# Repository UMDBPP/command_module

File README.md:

# ```</CMD>```

Command is the primary tracking payload flown by BPP. This repository contains design files and software required to run the current version of command.

Current POC:
Shipman

 ## Design Priciples
As the command module needs to fly on every flight mass reduction is a primary focus. For this reason a switch from perfboard to custom PCB's was done, and a substantial reduction in box volume is underway. Reliability is incredibly important and for this reason the payload operates its tracking systems in a full 4N redundant method.
### Tracking systems include (system/function):
#### 2x LiteAPRS 2m transmitters on 144.390 MHz
In flight position updates every minute. By nature of APRS tracking in hilly terrain unlikely to receive exact coordinates under 500m unless operating our own radios.
#### 1x SPOT Trace Tracker
COTS tracker from SPOT. Gives exact coordinates on landing.
#### 1x BITS (Balloon Iridium Telemetry System)
Exact coordinates throughout the flight, variable transmission rate 1min-15minutes (technically 10s-inf). Datalogger. XBee 900 HP allows for commands to be relayed through Iridium to other payloads and telemetry from payloads to be sent to ground. Possibility of ground to payload XBee communication without Iridium allowing for low latency high rate commanding.

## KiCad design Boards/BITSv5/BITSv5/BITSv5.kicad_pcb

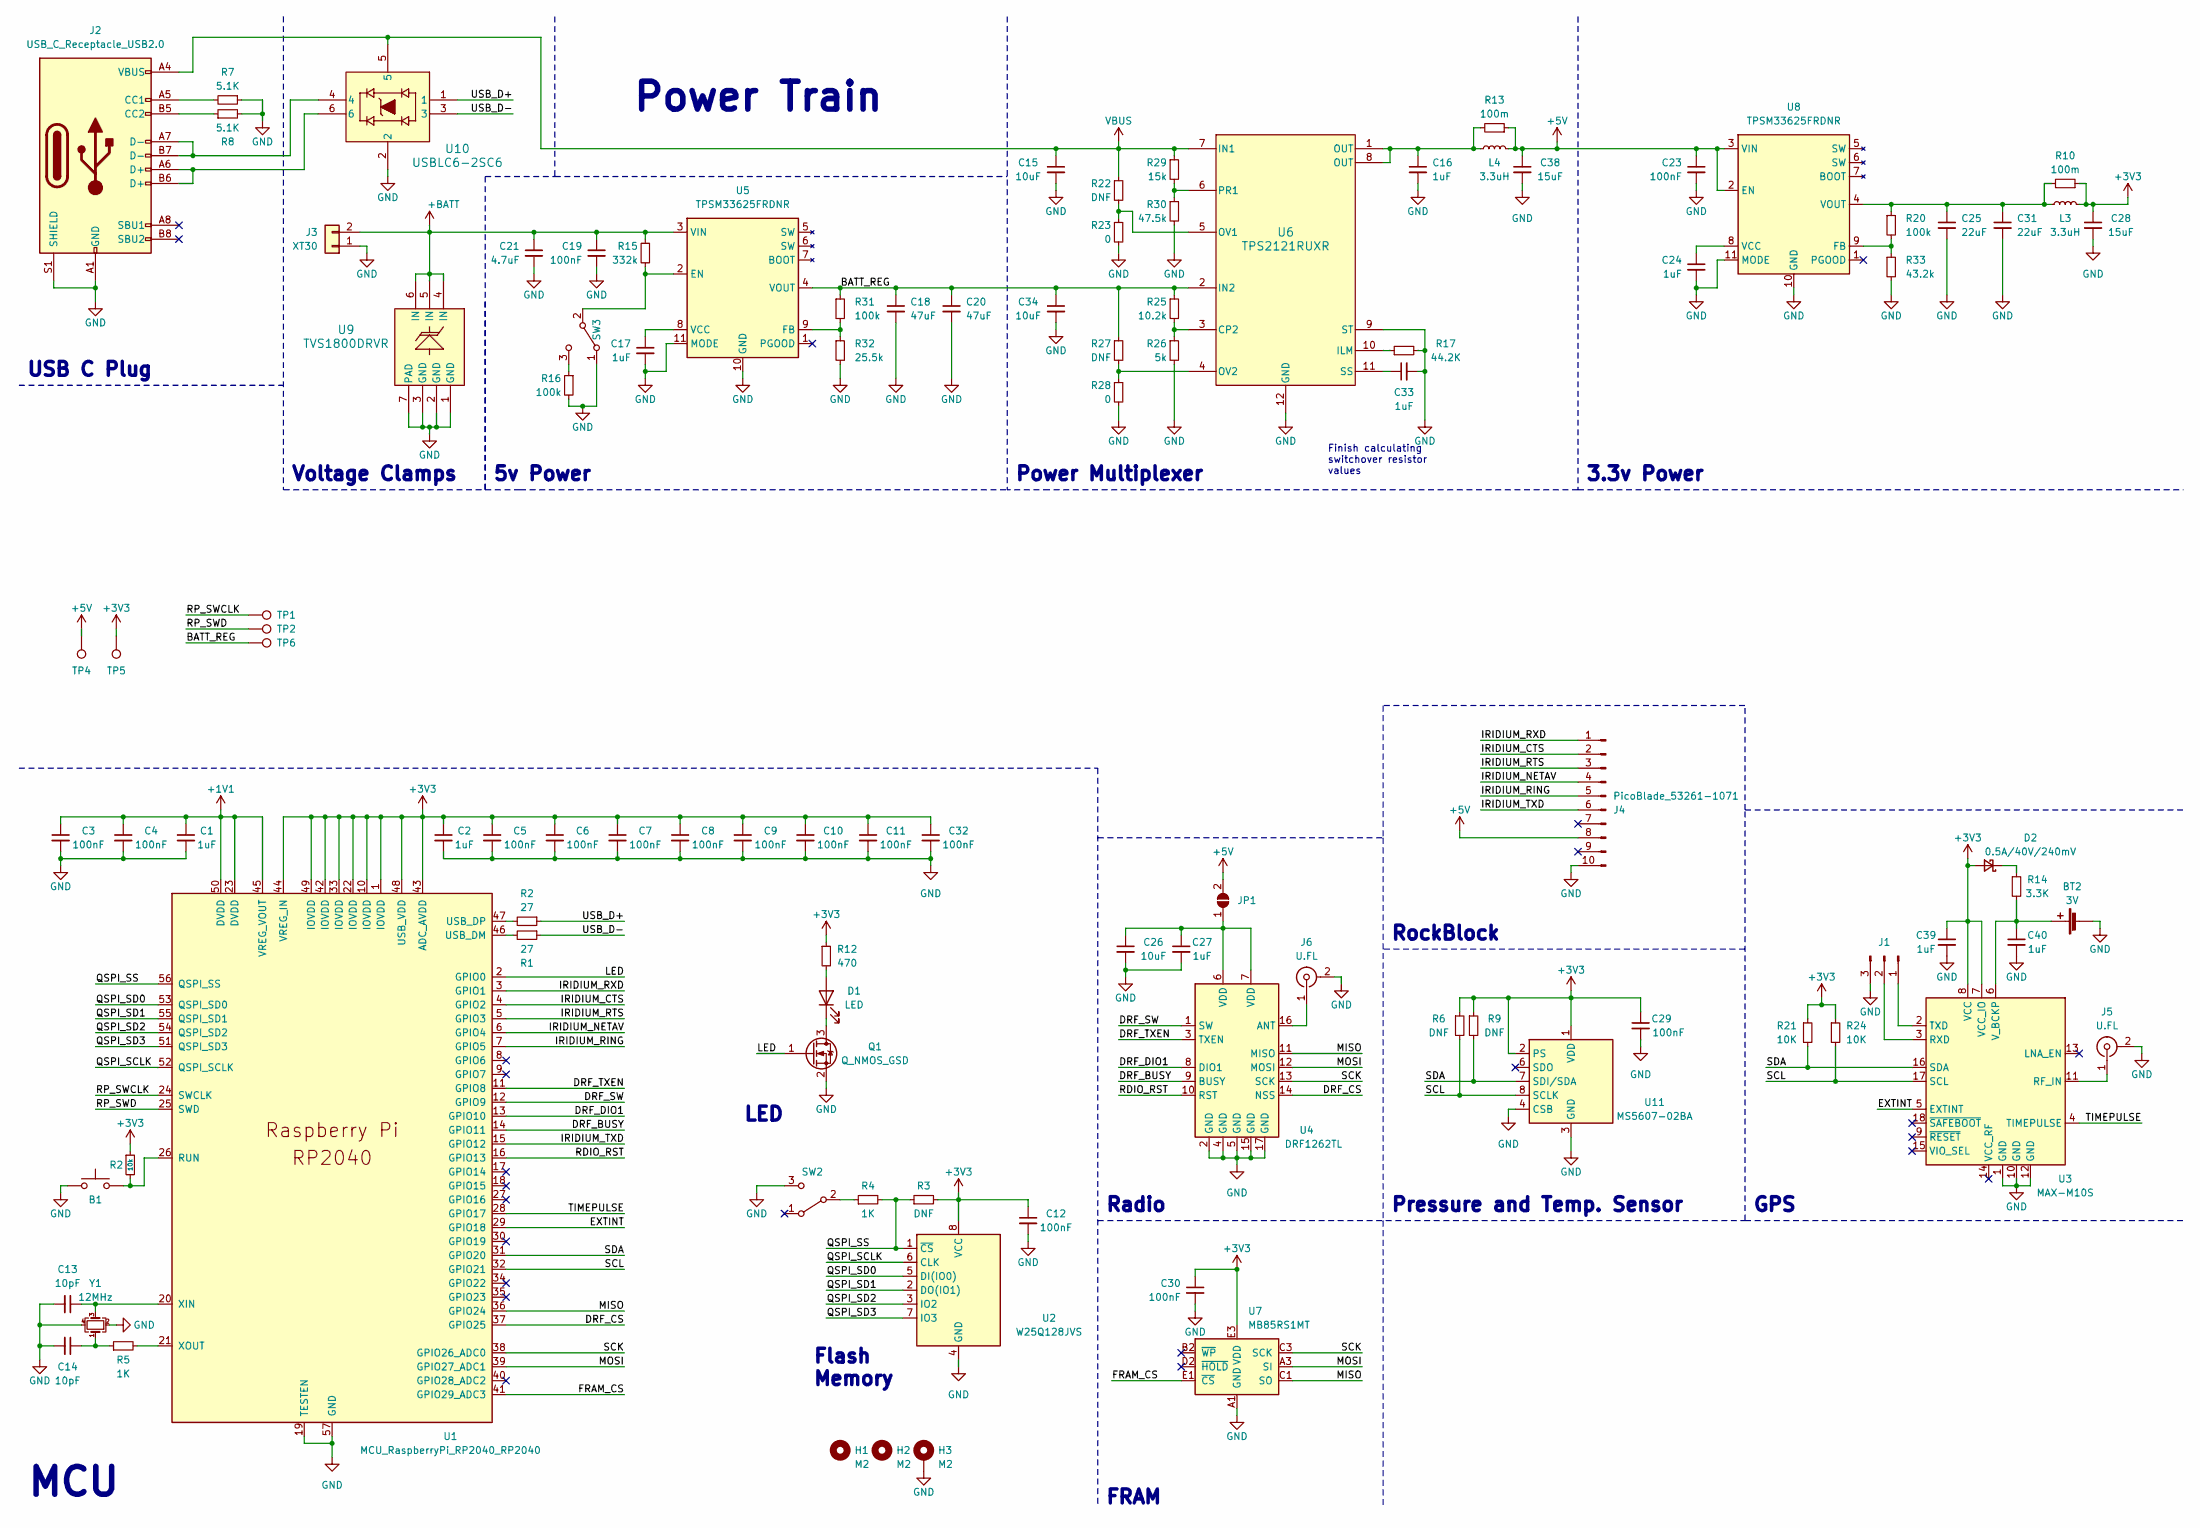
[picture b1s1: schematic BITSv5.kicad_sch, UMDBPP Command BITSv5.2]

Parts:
B1: KMR2; SW_Push_1P1T_NO_CK_KMR2
BT2: 3V; SEIKO_ML414H_IV01E
C1, C2: 1uF; C_0402_1005Metric
C3, C4, C5, C6, C7, C8, C9, C10, C11, C12, C32: 100nF; C_0402_1005Metric
C13, C14: 10pF; C_0402_1005Metric
C15, C26, C34: 10uF; C_0603_1608Metric
C16, C17, C24, C27, C33, C39, C40: 1uF; C_0603_1608Metric
C18, C20: 47uF; C_1206_3216Metric
C19, C23, C29, C30: 100nF; C_0603_1608Metric
C21: 4.7uF; C_0805_2012Metric
C25, C31: 22uF; C_0805_2012Metric
C28, C38: 15uF; C_1206_3216Metric
D1: LED; LED_0603_1608Metric
D2: 0.5A/40V/240mV; D_SOD-123F
H1, H2, H3: M2; MountingHole_2.2mm_M2_Pad
J1: Conn_01x03_Pin; PinHeader_1x03_P2.54mm_Vertical
J2: USB_C_Receptacle_USB2.0; USB_C_Receptacle_GCT_USB4105-xx-A_16P_TopMnt_Horizontal
J3: XT30; AMASS_XT30PW-M_1x02_P2.50mm_Horizontal
J4: PicoBlade_53261-1071; Molex_PicoBlade_53261-1071_1x10-1MP_P1.25mm_Horizontal
J5, J6: U.FL; U.FL_Molex_MCRF_73412-0110_Vertical
JP1: SolderJumper_2_Open; SolderJumper-2_P1.3mm_Open_RoundedPad1.0x1.5mm
L3, L4: 3.3uH; L_1210_3225Metric
Q1: Q_NMOS_GSD; SOT-23-3
R1: 27; R_0402_1005Metric
R2: 10k; R_0603_1608Metric
R3, R6, R9, R22, R27: DNF; R_0603_1608Metric
R4: 1K; R_0603_1608Metric
R5: 1K; R_0402_1005Metric
R7, R8: 5.1K; R_0603_1608Metric_Pad0.98x0.95mm_HandSolder
R10, R13: 100m; R_0603_1608Metric
R12: 470; R_0603_1608Metric
R14: 3.3K; R_0603_1608Metric
R15: 332k; R_0603_1608Metric
R16, R20, R31: 100k; R_0603_1608Metric
R17: 44.2K; R_0603_1608Metric
R21, R24: 10K; R_0603_1608Metric
R23, R28: 0; R_0603_1608Metric
R25: 10.2k; R_0603_1608Metric
R26: 5k; R_0603_1608Metric
R29: 15k; R_0603_1608Metric
R30: 47.5k; R_0603_1608Metric
R32: 25.5k; R_0603_1608Metric
R33: 43.2k; R_0603_1608Metric
SW2: CAS-120TB_NDC-M
SW3: SLIDE; CL-SB-12B-01_NDC
TP1, TP2: TestPoint; TestPoint_Pad_D2.0mm
TP4, TP5, TP6: TestPoint; TestPoint_Keystone_5000-5004_Miniature
U1: MCU_RaspberryPi_RP2040_RP2040; RP2040-QFN-56
U2: W25Q128JVS; WSON_128JVPIQ_WIN
U3: MAX-M10S; ublox_MAX
U4: DRF1262TL
U5, U8: TPSM33625FRDNR; RDN0011A-MFG-NO-VIA
U6: TPS2121RUXR; TPS2121
U7: MB85RS1MT; BGA8CP30X40_5X3_309X228X35B25N
U9: TVS1800DRVR; TVS1800
U10: USBLC6-2SC6; SOT23-6L_STM
U11: MS5607-02BA; LGA-8_3x5mm_P1.25mm
Y1: 12MHz; Crystal_SMD_2520-4Pin_2.5x2.0mm

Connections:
+1V1: C1.1, C3.1, C4.1, U1.23 (DVDD), U1.45 (VREG_VOUT), U1.50 (DVDD)
+5V: C23.1, C38.1, J4.8, JP1.2 (B), L4.1, R13.1, TP4.1, U8.2 (EN), U8.3 (VIN)
+BATT: C19.1, C21.1, J3.2, R15.1, U5.3 (VIN), U9.4 (IN), U9.5 (IN), U9.6 (IN)
/BATT_REG: C18.1, C20.1, C34.1, R25.1, R27.1, R31.1, TP6.1, U5.4 (VOUT), U6.2 (IN2)
/DRF_BUSY: U1.14 (GPIO11), U4.9 (BUSY)
/DRF_CS: U1.37 (GPIO25), U4.14 (NSS)
/DRF_DIO1: U1.13 (GPIO10), U4.8 (DIO1)
/DRF_SW: U1.12 (GPIO9), U4.1 (SW)
/DRF_TXEN: U1.11 (GPIO8), U4.3 (TXEN)
/EXTINT: U1.29 (GPIO18), U3.5 (EXTINT)
/FRAM_CS: U1.41 (GPIO29_ADC3), U7.E1 (~CS)
/IRIDIUM_CTS: J4.2, U1.4 (GPIO2)
/IRIDIUM_NETAV: J4.4, U1.6 (GPIO4)
/IRIDIUM_RING: J4.5, U1.7 (GPIO5)
/IRIDIUM_RTS: J4.3, U1.5 (GPIO3)
/IRIDIUM_RXD: J4.1, U1.3 (GPIO1)
/IRIDIUM_TXD: J4.6, U1.15 (GPIO12)
/LED: Q1.1 (G), U1.2 (GPIO0)
/MISO: U1.36 (GPIO24), U4.11 (MISO), U7.C1 (SO)
/MOSI: U1.39 (GPIO27_ADC1), U4.12 (MOSI), U7.A3 (SI)
/QSPI_SCLK: U1.52 (QSPI_SCLK), U2.6 (CLK)
/QSPI_SD0: U1.53 (QSPI_SD0), U2.5 (DI(IO0))
/QSPI_SD1: U1.55 (QSPI_SD1), U2.2 (DO(IO1))
/QSPI_SD2: U1.54 (QSPI_SD2), U2.3 (IO2)
/QSPI_SD3: U1.51 (QSPI_SD3), U2.7 (IO3)
/QSPI_SS: R3.1, R4.2, U1.56 (QSPI_SS), U2.1 (~CS)
/RDIO_RST: U1.16 (GPIO13), U4.10 (RST)
/RP_SWCLK: TP1.1, U1.24 (SWCLK)
/RP_SWD: TP2.1, U1.25 (SWD)
/SCK: U1.38 (GPIO26_ADC0), U4.13 (SCK), U7.C3 (SCK)
/SCL: R6.2, R24.2, U1.32 (GPIO21), U3.17 (SCL), U11.8 (SCLK)
/SDA: R9.2, R21.2, U1.31 (GPIO20), U3.16 (SDA), U11.7 (SDI/SDA)
/TIMEPULSE: U1.28 (GPIO17), U3.4 (TIMEPULSE)
/USB_D-: R1.1, U10.3
unnamed: BT2.1 (+), C40.1, R14.2, U3.6 (V_BCKP)
unnamed: C14.1, R5.1, Y1.1
unnamed: C16.1, L4.2, R13.2, U6.1 (OUT), U6.8 (OUT)
unnamed: D1.2 (A), R12.2
unnamed: D1.1 (K), Q1.3 (D)
unnamed: D2.1 (K), R14.1
unnamed: J1.1, U3.2 (TXD)
unnamed: J1.2, U3.3 (RXD)
unnamed: J2.A5 (CC1), R7.2
unnamed: J2.B5 (CC2), R8.1
unnamed: J2.A6 (D+), J2.B6 (D+), U10.6
unnamed: J2.A7 (D-), J2.B7 (D-), U10.4
unnamed: J5.1 (In), U3.11 (RF_IN)
unnamed: J6.1 (In), U4.16 (ANT)
unnamed: C26.1, C27.1, JP1.1 (A), U4.6 (VDD), U4.7 (VDD)
unnamed: R4.1, SW2.2 (B)
unnamed: R15.2, SW3.2 (B), U5.2 (EN)
unnamed: R16.1, SW3.3 (C)
unnamed: R1.2, U1.46 (USB_DM)
unnamed: C13.1, U1.20 (XIN), Y1.3
unnamed: R5.2, U1.21 (XOUT)
unnamed: R31.2, R32.1, U5.9 (FB)
unnamed: C17.1, U5.8 (VCC)
unnamed: R25.2, R26.1, U6.3 (CP2)
unnamed: R17.1, U6.10 (ILM)
unnamed: R22.2, R23.1, U6.5 (OV1)
unnamed: R27.2, R28.1, U6.4 (OV2)
unnamed: R29.2, R30.1, U6.6 (PR1)
unnamed: C33.1, U6.11 (SS)
unnamed: R20.2, R33.1, U8.9 (FB)
unnamed: C24.1, U8.8 (VCC)
unnamed: C25.1, C31.1, L3.2, R10.2, R20.1, U8.4 (VOUT)
VBUS: C15.1, J2.A4 (VBUS), J2.A9 (VBUS), J2.B4 (VBUS), J2.B9 (VBUS), R22.1, R29.1, U6.7 (IN1), U10.5

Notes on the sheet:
Pressure and Temp. Sensor
Power Train
USB C Plug
FRAM
3.3v Power
Finish calculating switchover resistor values
GPS
Power Multiplexer
LED
RockBlock
Voltage Clamps
Flash Memory
MCU
Radio
5v Power

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
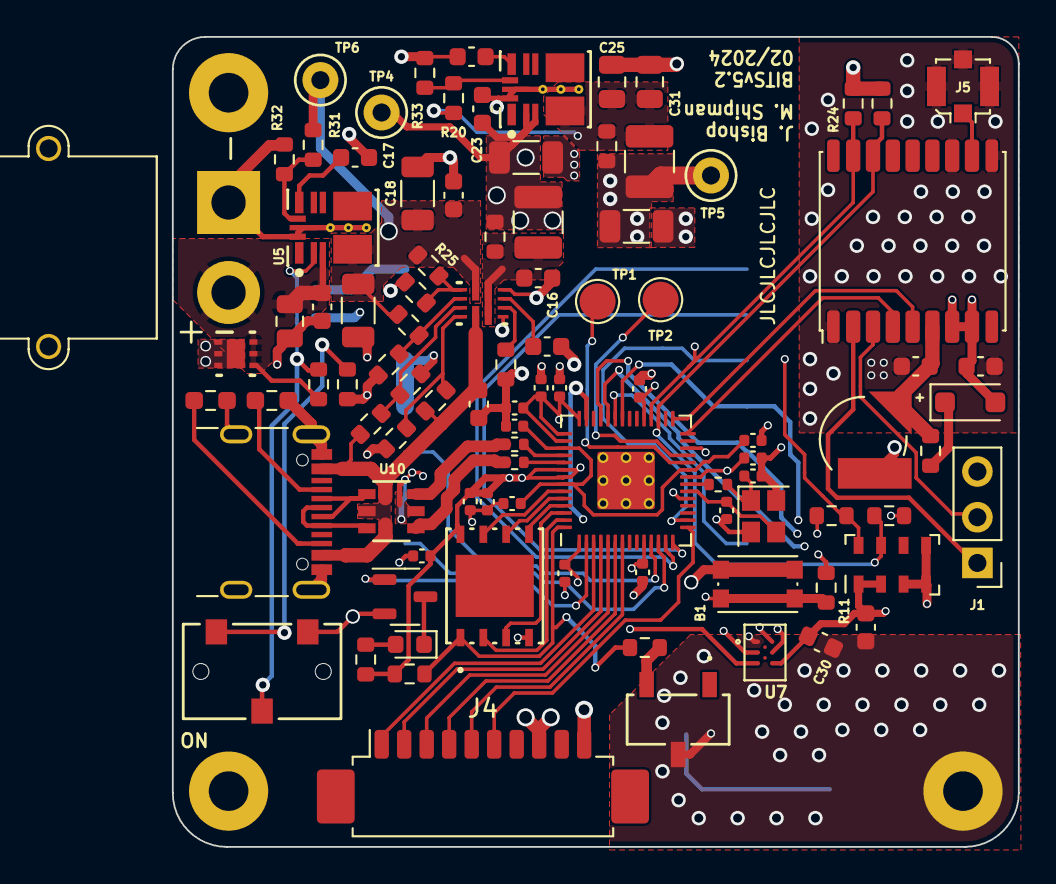
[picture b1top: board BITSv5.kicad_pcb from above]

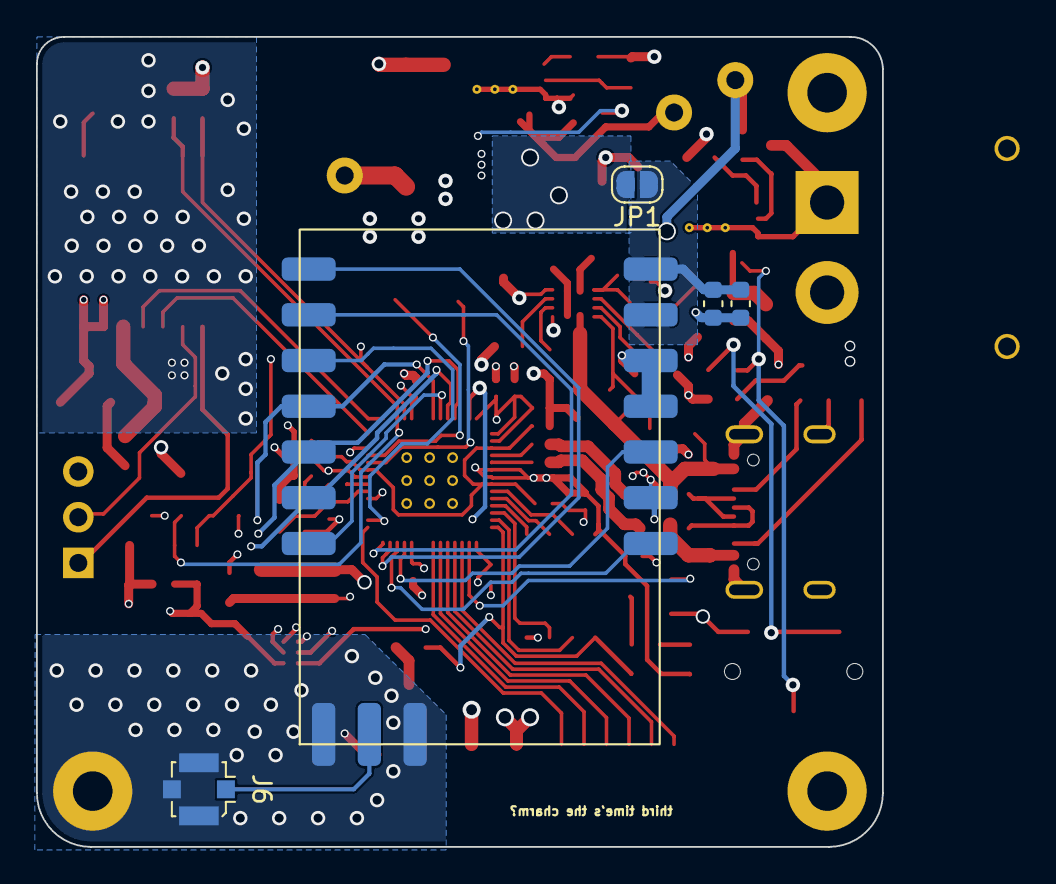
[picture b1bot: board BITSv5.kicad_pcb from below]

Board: 4 copper layers, 47.0 x 45.0 mm, 103 parts (5 on the bottom side), 72 nets.

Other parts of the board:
R11: 10k; R_0603_1608Metric

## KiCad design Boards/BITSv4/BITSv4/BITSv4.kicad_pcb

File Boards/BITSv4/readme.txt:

Folder for BITSv4 development
Starting 10/3/2021,
jmolter

Work based on lessons from BITSv3

---Focus Areas---

-Reg LMR16020-
Keep the IC
Change inductor for easier assembly
Consider chaning output to 5v,
OR source 5v from another source

-Misc.-
Change power connector to match LightAPRS LVC

Change picoblade to right angle

Remove celltracker crosstalk conn

Consider GPS improvements

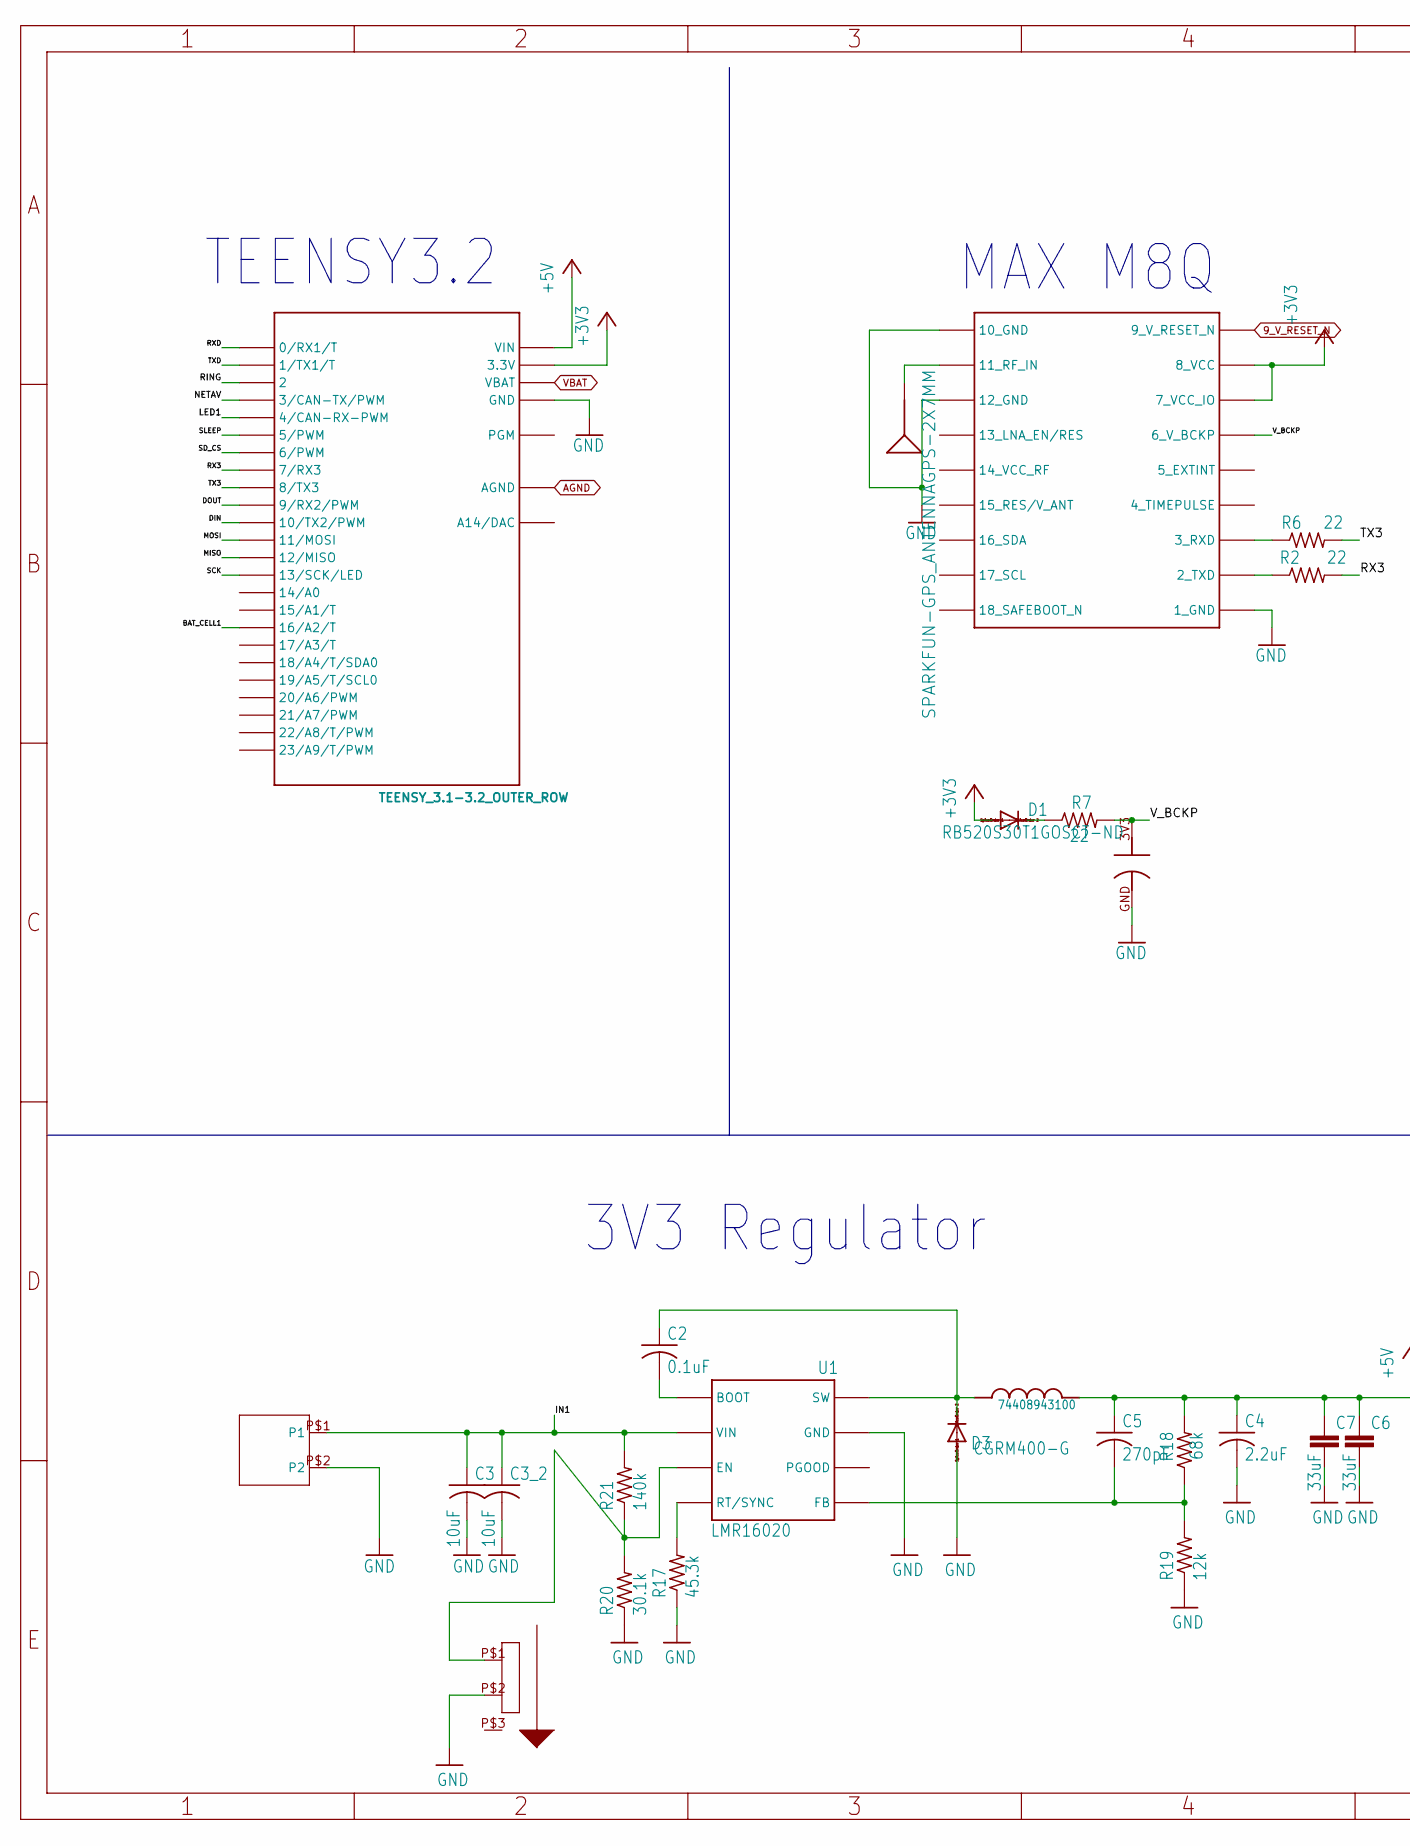
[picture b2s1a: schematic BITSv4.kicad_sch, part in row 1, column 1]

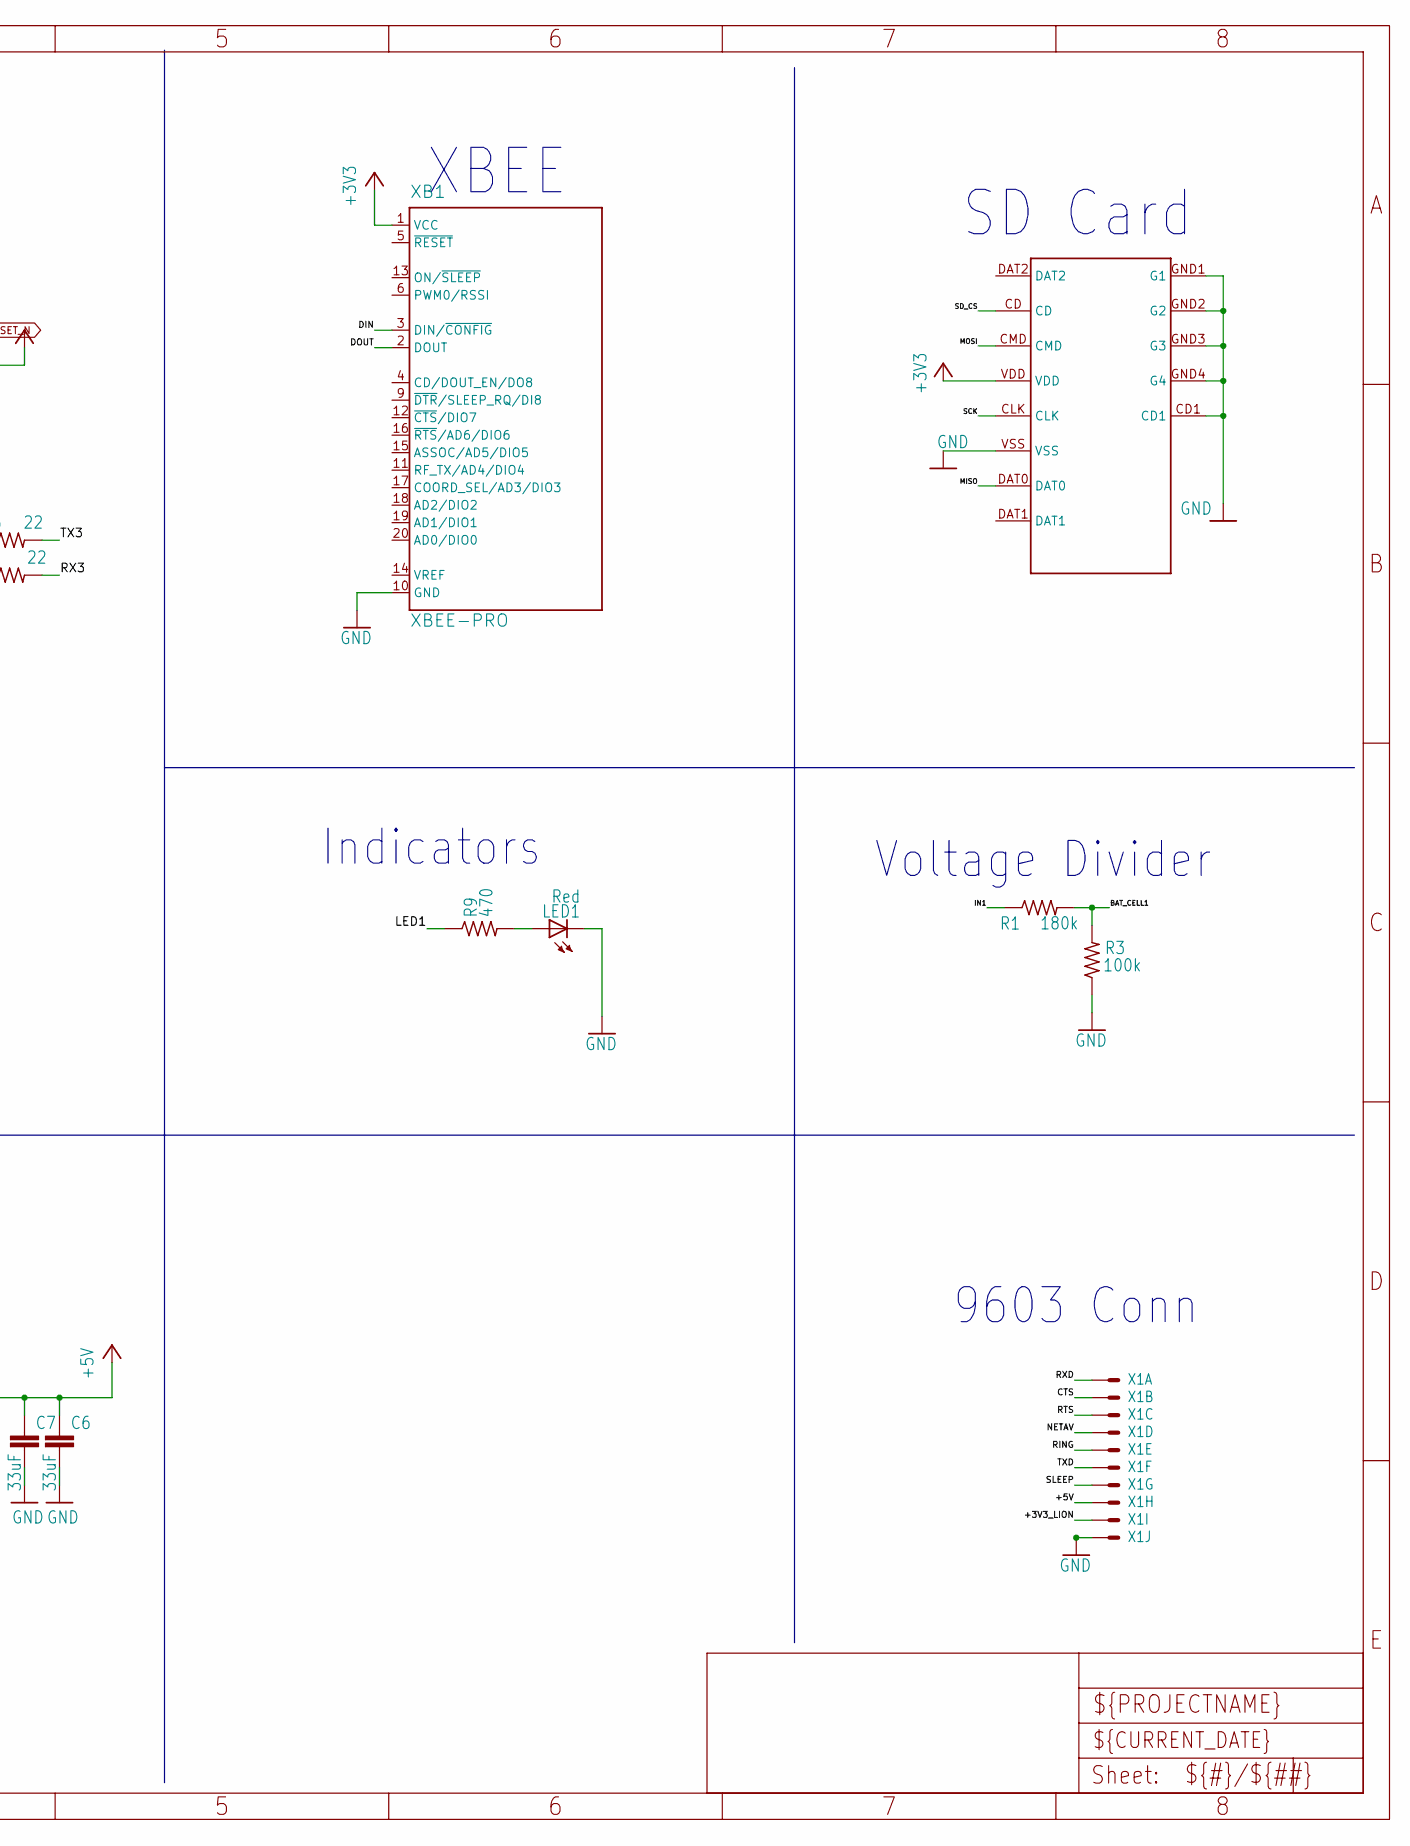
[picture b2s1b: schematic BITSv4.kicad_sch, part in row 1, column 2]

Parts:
C1: 0.2F; ELNASUPERCAP
C2: 0.1uF; C0603
C3, C3_2: 10uF; C0805
C4: 2.2uF; C0603
C5: 270pF; C0402
C6, C7: 33uF; C050-024X044
D1: RB520S30T1GOSCT-ND; SOD523
D3: CGRM400-G; SOD-123_MINI-SMA
L1: 74408943100
LED1: Red; CHIP-LED0603
R1: 180k; R0603
R2, R6, R7: 22; R0603
R3: 100k; R0603
R9: 470; R0603
R17: 45.3k; R0603
R18: 68k; R0603
R19: 12k; R0603
R20: 30.1k; R0603
R21: 140k; R0603
U1: LMR16020; SO8
U$1: 559350210
U$2: TEENSY_3.1-3.2_OUTER_ROW; TEENSY_3.0-3.2&LC_OUTER_ROW
U$3: CL-SB-12B-01
U$4: MICRO_SD; MICRO_SD_HINGED
U$7: MAX-M8
U$8: SPARKFUN-GPS_ANTENNAGPS-2X7MM; SPARKFUN-GPS_ANT-GPS-2X7MM
X1: 53?-10261; 53261-10
XB1: XBEE-PRO

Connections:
9_V_RESET_N: U$7.9_RESET_N (9_V_RESET_N)
+3V3: D1.A, U$2.3.3V, U$2.3.3V1 (3.3V), U$4.VDD, U$7.7_VCC_IO, U$7.8_VCC, XB1.1 (VCC)
+3V3_LION: X1.9
+5V: C4.1, C5.1, C6.1, C7.1, L1.P$2, R18.2, U$2.VIN, X1.8
AGND: U$2.AGND
BAT_CELL1: R1.2, R3.2, U$2.16/A2 (16/A2/T)
CTS: X1.2
DIN: U$2.10 (10/TX2/PWM), XB1.3 (DIN/~CONFIG)
DOUT: U$2.9 (9/RX2/PWM), XB1.2 (DOUT)
FB: C5.2, R18.1, R19.2, U1.P$5 (FB)
GND: C1.GND, C3.2, C3_2.2, C4.2, C6.2, C7.2, D3.A, LED1.C, R3.1, R17.1, R19.1, R20.1, U1.P$7 (GND), U1.PAD (GND), U$1.P$2 (P2), U$2.GND, U$2.GND1 (GND), U$3.P$2 (P2), U$4.CD1, U$4.GND1 (G1), U$4.GND2 (G2), U$4.GND3 (G3), U$4.GND4 (G4), U$4.VSS, U$7.1_GND, U$7.10_GND, U$7.12_GND, X1.10, XB1.10 (GND)
IN1: C3.1, C3_2.1, R1.1, R21.2, U1.P$2 (VIN), U$1.P$1 (P1)
LED1: R9.1, U$2.4 (4/CAN-RX-PWM)
MISO: U$2.12 (12/MISO), U$4.DAT0
MOSI: U$2.11 (11/MOSI), U$4.CMD
unnamed: U$7.11_RF_IN, U$8.1
unnamed: D1.C, R7.1
unnamed: R6.1, U$7.3_RXD
unnamed: R2.1, U$7.2_TXD
unnamed: LED1.A, R9.2
unnamed: R20.2, R21.1, U1.P$3 (EN), U$3.P$1 (P1)
unnamed: R17.2, U1.P$4 (RT/SYNC)
unnamed: C2.2, U1.P$1 (BOOT)
NETAV: U$2.3 (3/CAN-TX/PWM), X1.4
RING: U$2.2, X1.5
RTS: X1.3
RX3: R2.2, U$2.7 (7/RX3)
RXD: U$2.0 (0/RX1/T), X1.1
SCK: U$2.13 (13/SCK/LED), U$4.CLK
SD_CS: U$2.6 (6/PWM), U$4.CD
SLEEP: U$2.5 (5/PWM), X1.7
SW: C2.1, D3.C, L1.P$1, U1.P$8 (SW)
TX3: R6.2, U$2.8 (8/TX3)
TXD: U$2.1 (1/TX1/T), X1.6
VBAT: U$2.VBAT
V_BCKP: C1.3V3, R7.2, U$7.6_V_BCKP

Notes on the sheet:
SD Card
XBEE
Indicators
9603 Conn
3V3 Regulator
TEENSY3.2
MAX M8Q
Voltage Divider

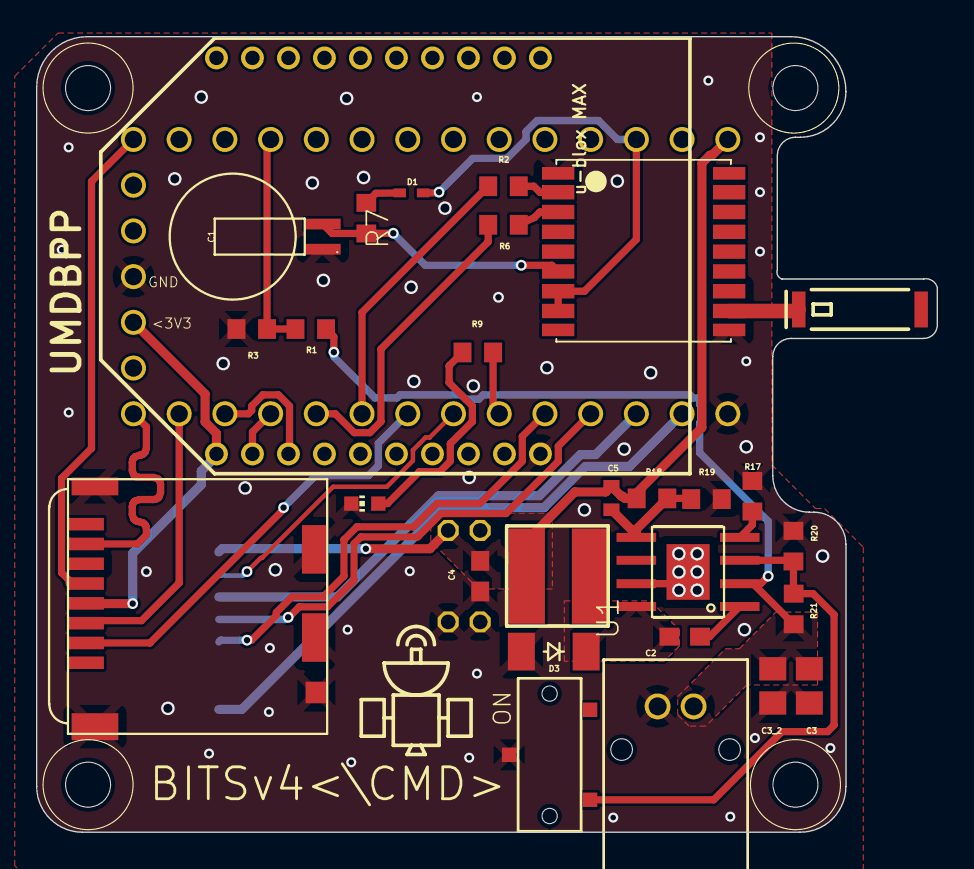
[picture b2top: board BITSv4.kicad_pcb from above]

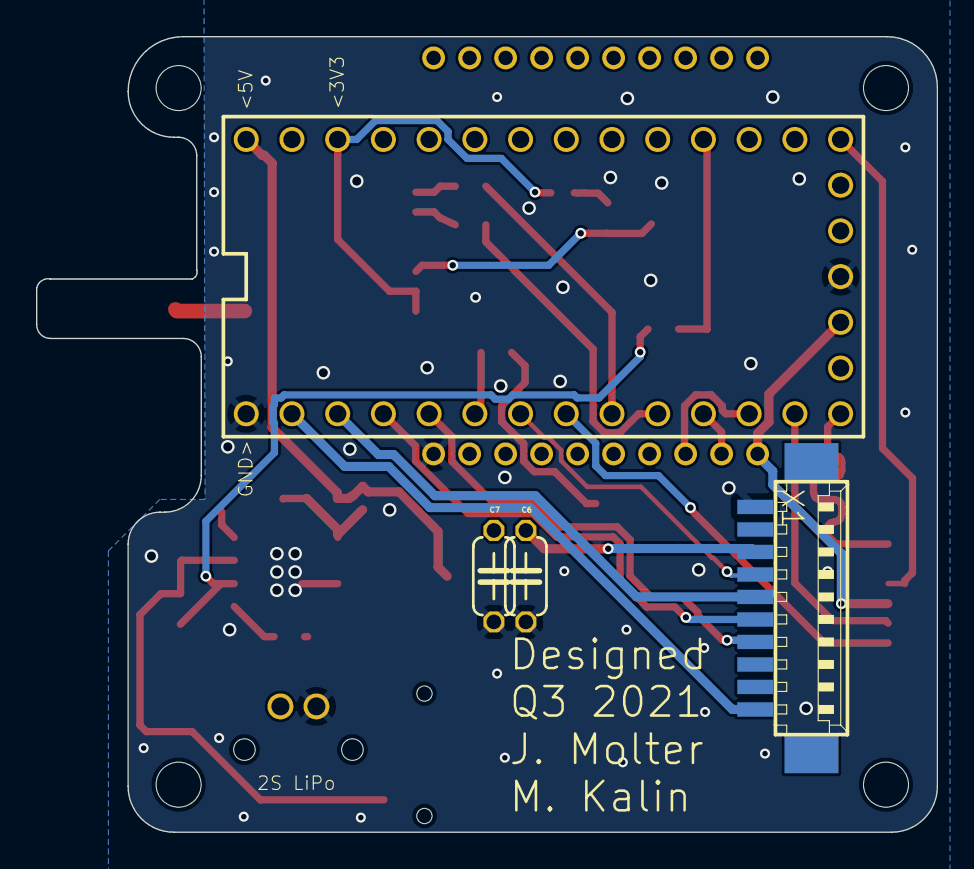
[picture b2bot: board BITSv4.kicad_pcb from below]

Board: 2 copper layers, 50.0 x 44.2 mm, 36 parts (4 on the bottom side), 30 nets.

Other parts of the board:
@HOLE0, @HOLE1, @HOLE2, @HOLE3: (no value)

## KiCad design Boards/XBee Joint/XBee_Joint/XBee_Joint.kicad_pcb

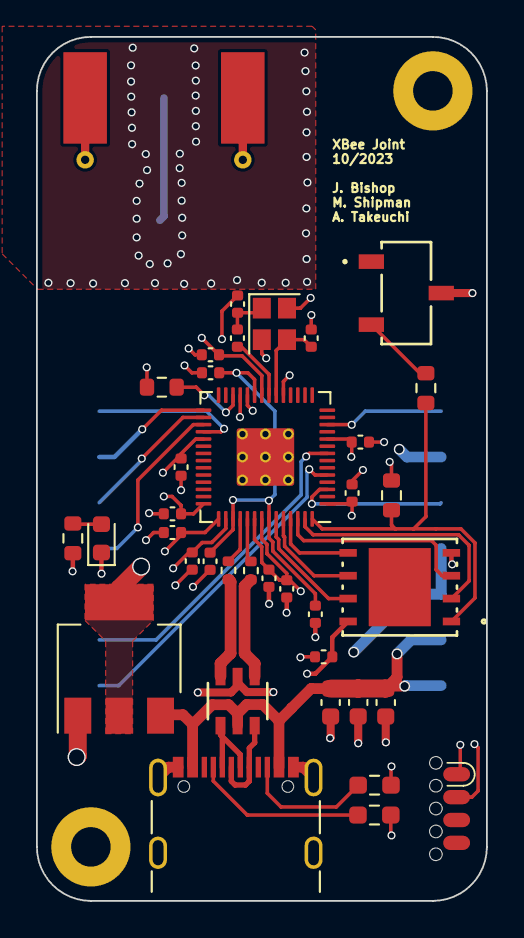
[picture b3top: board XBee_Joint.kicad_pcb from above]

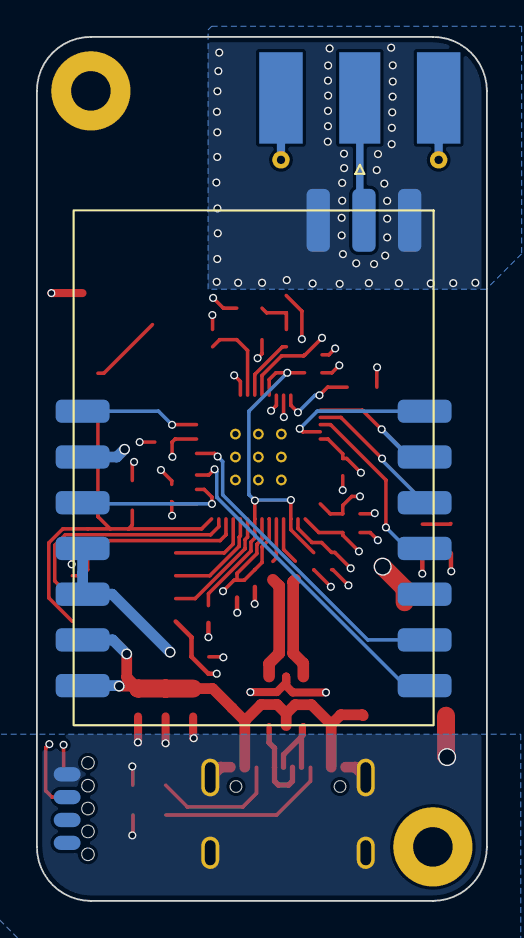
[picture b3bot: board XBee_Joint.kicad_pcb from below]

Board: 4 copper layers, 25.0 x 48.0 mm, 40 parts (2 on the bottom side), 35 nets.

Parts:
AE1: Antenna; SMA_Molex_73251-1153_EdgeMount_Horizontal
C1, C4, C7, C8, C9, C10, C11, C12, C13, C14, C15: 100nF; C_0402_1005Metric
C2, C3: 10pF; C_0402_1005Metric
C5, C6: 1uF; C_0402_1005Metric
C16: 1uF; C_0603_1608Metric
C17: 100nF; C_0603_1608Metric
C18: 10uF; C_0603_1608Metric
D1: LED; LED_0603_1608Metric
H1, H2: M2; MountingHole_2.2mm_M2_Pad
J1: SOICbite; SOIC_clipProgSmall
J2: USB_C_Receptacle_USB2.0; USB_C_Receptacle_GCT_USB4105-xx-A_16P_TopMnt_Horizontal
R1: 1K; C_0402_1005Metric
R2, R3: 27; R_0402_1005Metric
R4: 10K; R_0603_1608Metric
R6: 470; R_0603_1608Metric
R7: 1K; R_0603_1608Metric
R8: DNF; R_0603_1608Metric
R9, R10: 5.1K; R_0603_1608Metric_Pad0.98x0.95mm_HandSolder
SW2: CAS-120TB_NDC-M
U1: MCU_RaspberryPi_RP2040_RP2040; RP2040-QFN-56
U2: AP2114H-3.3TRG1; SOT-223-3_TabPin2
U3: DRF1262TL
U4: W25Q128JVS; WSON_128JVPIQ_WIN
U5: USBLC6-2SC6; SOT23-6L_STM
Y1: 12MHz; Crystal_SMD_2520-4Pin_2.5x2.0mm

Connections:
+1V1: C1.1, C4.1, C5.1, U1.23 (DVDD), U1.45 (VREG_VOUT), U1.50 (DVDD)
+3V3: C6.1, C7.1, C8.1, C9.1, C10.1, C11.1, C12.1, C13.1, C14.1, C15.1, R4.1, R6.1, R8.2, U1.1 (IOVDD), U1.10 (IOVDD), U1.22 (IOVDD), U1.33 (IOVDD), U1.42 (IOVDD), U1.43 (ADC_AVDD), U1.44 (VREG_IN), U1.48 (USB_VDD), U1.49 (IOVDD), U2.2 (VO), U4.8 (VCC)
/DRF_BUSY: U1.8 (GPIO6), U3.9 (BUSY)
/DRF_CLK: U1.29 (GPIO18), U3.13 (SCK)
/DRF_CS: U1.32 (GPIO21), U3.14 (NSS)
/DRF_DIO1: U1.5 (GPIO3), U3.8 (DIO1)
/DRF_MISO: U1.31 (GPIO20), U3.11 (MISO)
/DRF_MOSI: U1.30 (GPIO19), U3.12 (MOSI)
/DRF_SW: U1.12 (GPIO9), U3.1 (SW)
/DRF_TXEN: U1.3 (GPIO1), U3.3 (TXEN)
/QSPI_SCLK: U1.52 (QSPI_SCLK), U4.6 (CLK)
/QSPI_SD0: U1.53 (QSPI_SD0), U4.5 (DI(IO0))
/QSPI_SD1: U1.55 (QSPI_SD1), U4.2 (DO(IO1))
/QSPI_SD2: U1.54 (QSPI_SD2), U4.3 (IO2)
/QSPI_SD3: U1.51 (QSPI_SD3), U4.7 (IO3)
/QSPI_SS: R7.2, R8.1, U1.56 (QSPI_SS), U4.1 (~CS)
/RP_SWCLK: J1.1, U1.24 (SWCLK)
/RP_SWD: J1.2, U1.25 (SWD)
/USB_D+: R2.1, U5.1
/USB_D-: R3.1, U5.3
GND: C1.2, C2.2, C3.2, C4.2, C5.2, C6.2, C7.2, C8.2, C9.2, C10.2, C11.2, C12.2, C13.2, C14.2, C15.2, C16.2, C17.2, C18.2, D1.1 (K), J1.8, J2.A1 (GND), J2.A12 (GND), J2.B1 (GND), J2.B12 (GND), J2.S1 (SHIELD), R9.1, R10.2, SW2.3 (C), U1.19 (TESTEN), U1.57 (GND), U2.1 (GND), U3.2 (GND), U3.4 (GND), U3.5 (GND), U3.15 (GND), U3.17 (GND), U4.4 (GND), U5.2, Y1.2, Y1.4
unnamed: AE1.1 (A), U3.16 (ANT)
unnamed: C3.1, R1.1, Y1.1
unnamed: D1.2 (A), R6.2
unnamed: J2.A5 (CC1), R9.2
unnamed: J2.B5 (CC2), R10.1
unnamed: J2.A6 (D+), J2.B6 (D+), U5.6
unnamed: J2.A7 (D-), J2.B7 (D-), U5.4
unnamed: R7.1, SW2.2 (B)
unnamed: R4.2, U1.26 (RUN)
unnamed: R3.2, U1.46 (USB_DM)
unnamed: R2.2, U1.47 (USB_DP)
unnamed: C2.1, U1.20 (XIN), Y1.3
unnamed: R1.2, U1.21 (XOUT)
VBUS: C16.1, C17.1, C18.1, J2.A4 (VBUS), J2.A9 (VBUS), J2.B4 (VBUS), J2.B9 (VBUS), U2.3 (VI), U3.6 (VDD), U3.7 (VDD), U5.5
